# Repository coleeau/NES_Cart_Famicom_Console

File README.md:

# NES Cartridge Famicom Console
An adapter to use NES cartridges on a Famicom

## Why
Primarily so i can use NES Games that are either NES exclusive (ie Tetris) or cheaper overall (ie accounting for shipping and import fees)

## Why not buy one
a few reasons here
- Harder to find than the adapter for the other way around
- ones you can find are too expensive, and are bare pcb
- all existing ones have the cartridge vertically. wobble will be bad for connection and it looks stupid
- many existing ones lack expansion audio and other issues

## Goal for adapter
- Horizontal orientation for adapter (think famicom network adapter meets Blinking Light Win)
- support for either no expansion audio OR expansion audio on EXP6 or EXP9
- support for cartridges that requite CIRAM /CE and PPU /A14 to be sepearate

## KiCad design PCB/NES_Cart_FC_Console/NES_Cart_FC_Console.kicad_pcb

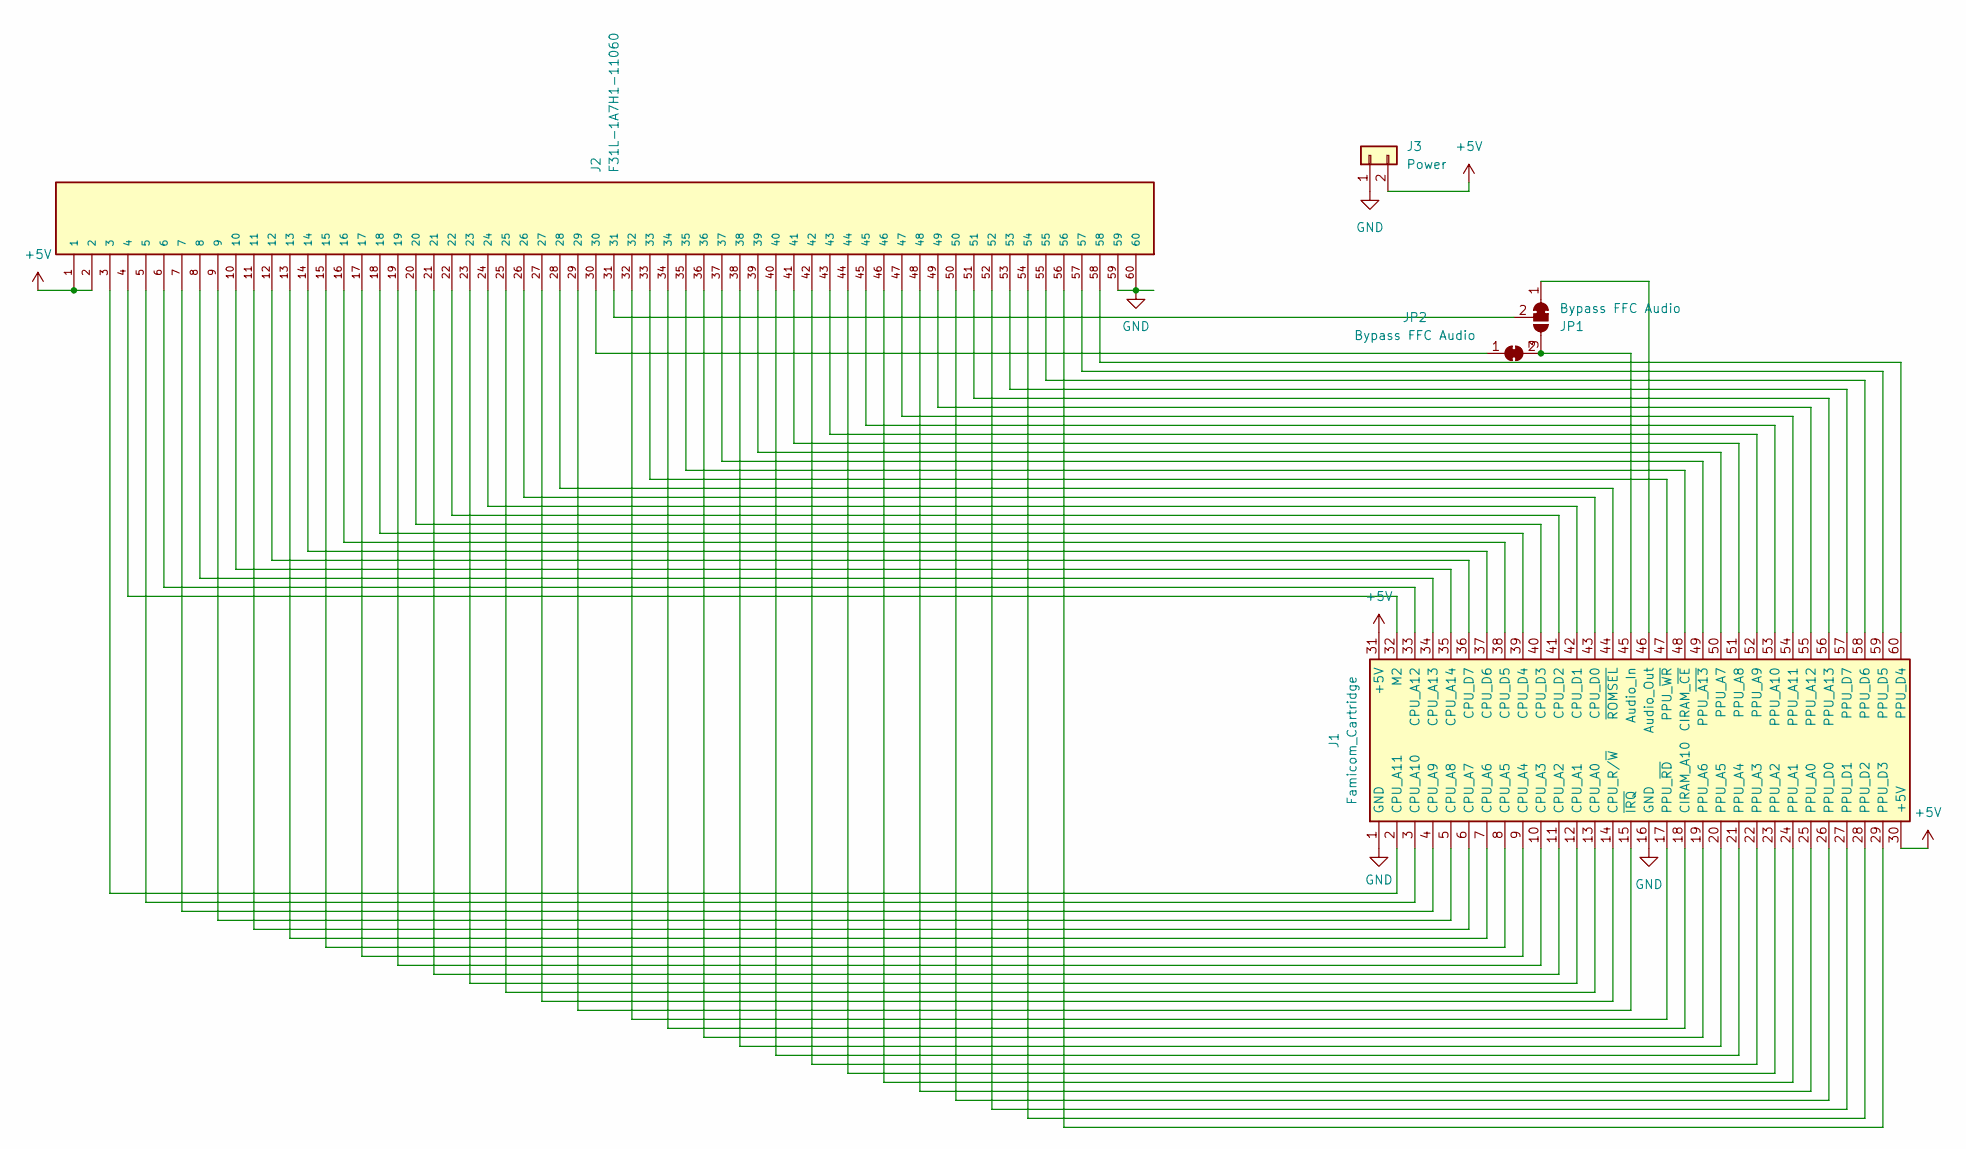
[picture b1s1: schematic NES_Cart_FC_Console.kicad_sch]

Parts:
J1: Famicom_Cartridge; Famicom_Card_Edge
J2: F31L-1A7H1-11060; AMPHENOL_F31L-1A7H1-11060; PARTREV F31L-1A7H1-11060
J3: Power; PinSocket_1x02_P2.54mm_Vertical
JP1: Bypass FFC Audio; SolderJumper-3_P1.3mm_Bridged2Bar12_RoundedPad1.0x1.5mm_Num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
JP2: Bypass FFC Audio; SolderJumper-2_P1.3mm_Bridged_RoundedPad1.0x1.5mm

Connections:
+5V: J1.30 (+5V), J1.31 (+5V), J2.1, J2.2, J3.2
GND: J1.1 (GND), J1.16 (GND), J2.59, J2.60, J3.1
unnamed: J1.45 (Audio_In), JP1.3 (B), JP2.2 (B)
unnamed: J1.46 (Audio_Out), JP1.1 (A)
unnamed: J1.18 (CIRAM_A10), J2.34
unnamed: J1.48 (CIRAM_~CE), J2.35
unnamed: J1.13 (CPU_A0), J2.25
unnamed: J1.12 (CPU_A1), J2.23
unnamed: J1.11 (CPU_A2), J2.21
unnamed: J1.10 (CPU_A3), J2.19
unnamed: J1.9 (CPU_A4), J2.17
unnamed: J1.8 (CPU_A5), J2.15
unnamed: J1.7 (CPU_A6), J2.13
unnamed: J1.6 (CPU_A7), J2.11
unnamed: J1.5 (CPU_A8), J2.9
unnamed: J1.4 (CPU_A9), J2.7
unnamed: J1.3 (CPU_A10), J2.5
unnamed: J1.2 (CPU_A11), J2.3
unnamed: J1.33 (CPU_A12), J2.6
unnamed: J1.34 (CPU_A13), J2.8
unnamed: J1.35 (CPU_A14), J2.10
unnamed: J1.43 (CPU_D0), J2.26
unnamed: J1.42 (CPU_D1), J2.24
unnamed: J1.41 (CPU_D2), J2.22
unnamed: J1.40 (CPU_D3), J2.20
unnamed: J1.39 (CPU_D4), J2.18
unnamed: J1.38 (CPU_D5), J2.16
unnamed: J1.37 (CPU_D6), J2.14
unnamed: J1.36 (CPU_D7), J2.12
unnamed: J1.14 (CPU_R/~W), J2.27
unnamed: J1.32 (M2), J2.4
unnamed: J1.25 (PPU_A0), J2.48
unnamed: J1.24 (PPU_A1), J2.46
unnamed: J1.23 (PPU_A2), J2.44
unnamed: J1.22 (PPU_A3), J2.42
unnamed: J1.21 (PPU_A4), J2.40
unnamed: J1.20 (PPU_A5), J2.38
unnamed: J1.19 (PPU_A6), J2.36
unnamed: J1.50 (PPU_A7), J2.39
unnamed: J1.51 (PPU_A8), J2.41
unnamed: J1.52 (PPU_A9), J2.43
unnamed: J1.53 (PPU_A10), J2.45
unnamed: J1.54 (PPU_A11), J2.47
unnamed: J1.55 (PPU_A12), J2.49
unnamed: J1.56 (PPU_A13), J2.51
unnamed: J1.26 (PPU_D0), J2.50
unnamed: J1.27 (PPU_D1), J2.52
unnamed: J1.28 (PPU_D2), J2.54
unnamed: J1.29 (PPU_D3), J2.56
unnamed: J1.60 (PPU_D4), J2.58
unnamed: J1.59 (PPU_D5), J2.57
unnamed: J1.58 (PPU_D6), J2.55
unnamed: J1.57 (PPU_D7), J2.53
unnamed: J1.49 (PPU_~A13), J2.37
unnamed: J1.17 (PPU_~RD), J2.32
unnamed: J1.47 (PPU_~WR), J2.33
unnamed: J1.15 (~IRQ), J2.29
unnamed: J1.44 (~ROMSEL), J2.28
unnamed: J2.31, JP1.2 (C)
unnamed: J2.30, JP2.1 (A)

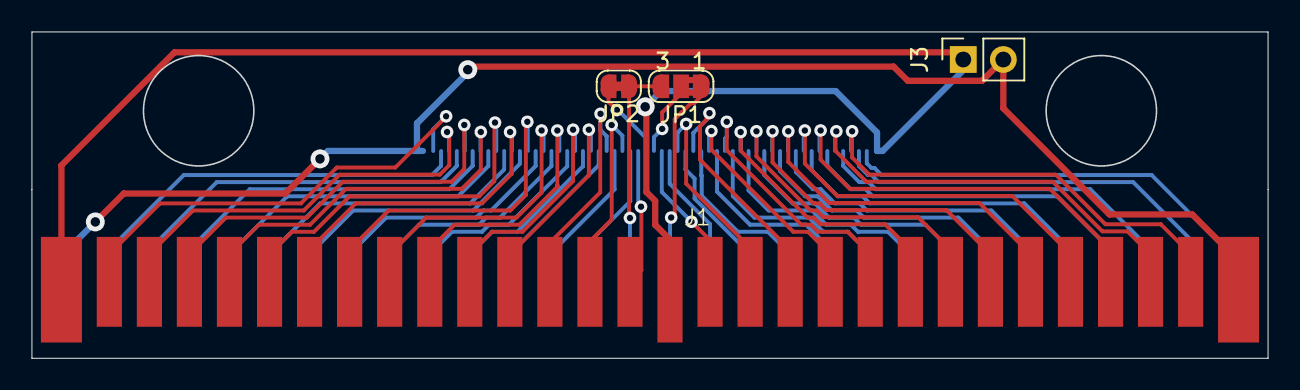
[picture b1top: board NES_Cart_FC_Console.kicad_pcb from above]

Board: 2 copper layers, 78.3 x 20.7 mm, 5 parts (1 on the bottom side), 60 nets.

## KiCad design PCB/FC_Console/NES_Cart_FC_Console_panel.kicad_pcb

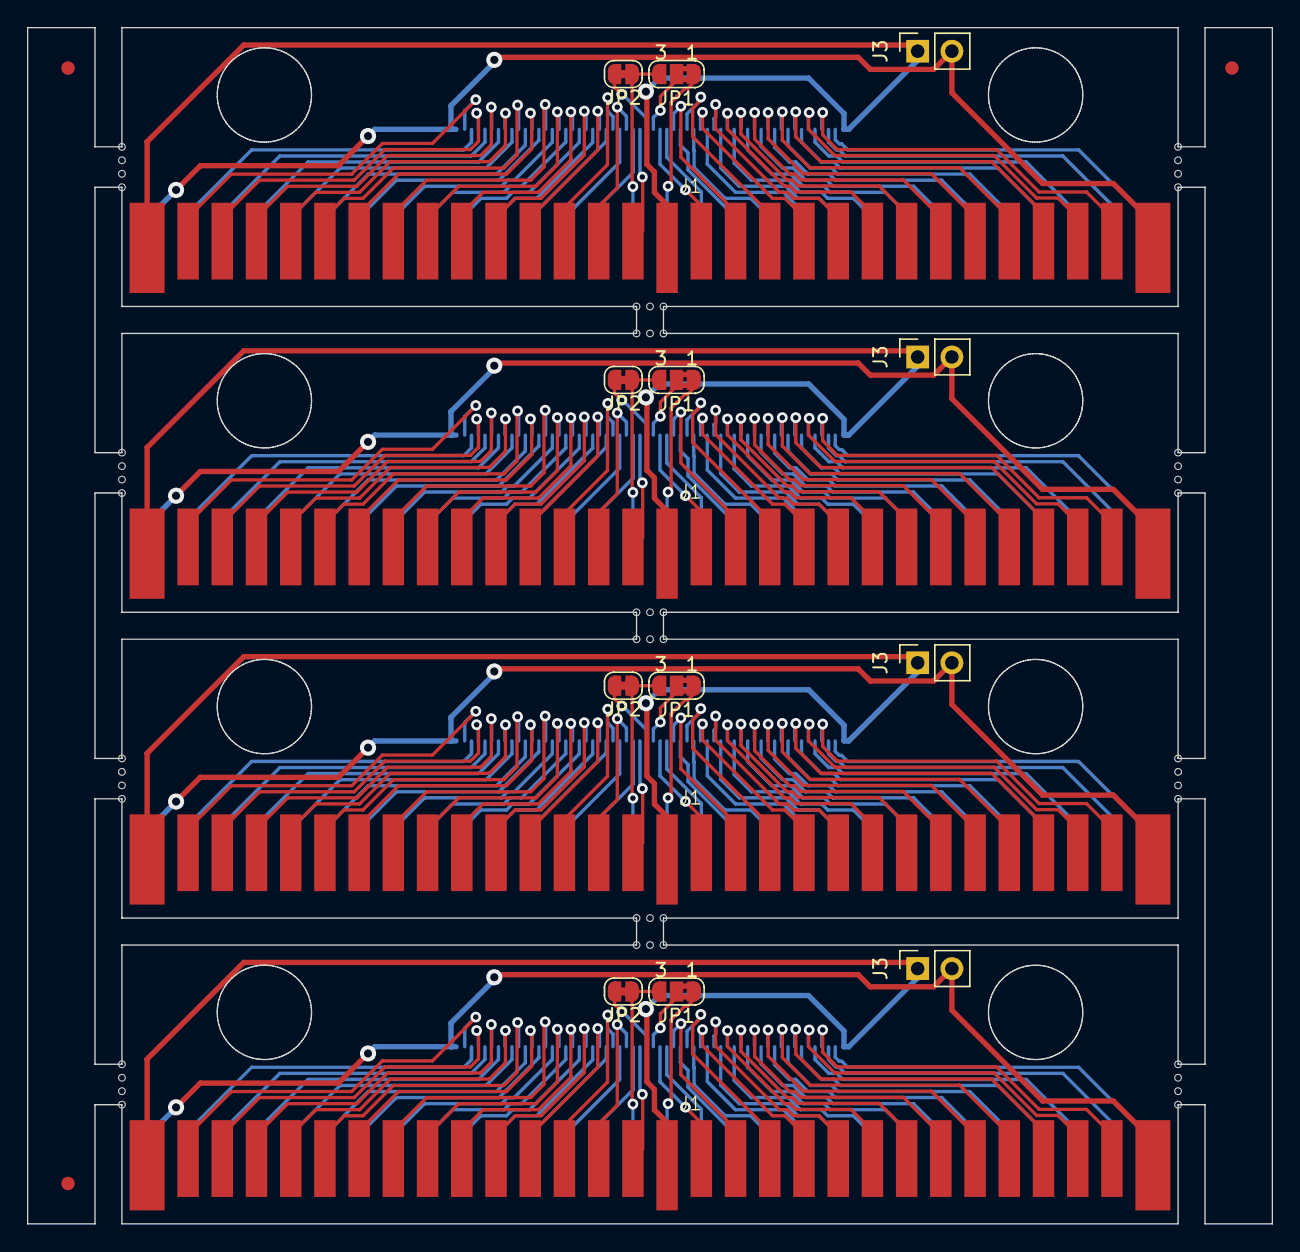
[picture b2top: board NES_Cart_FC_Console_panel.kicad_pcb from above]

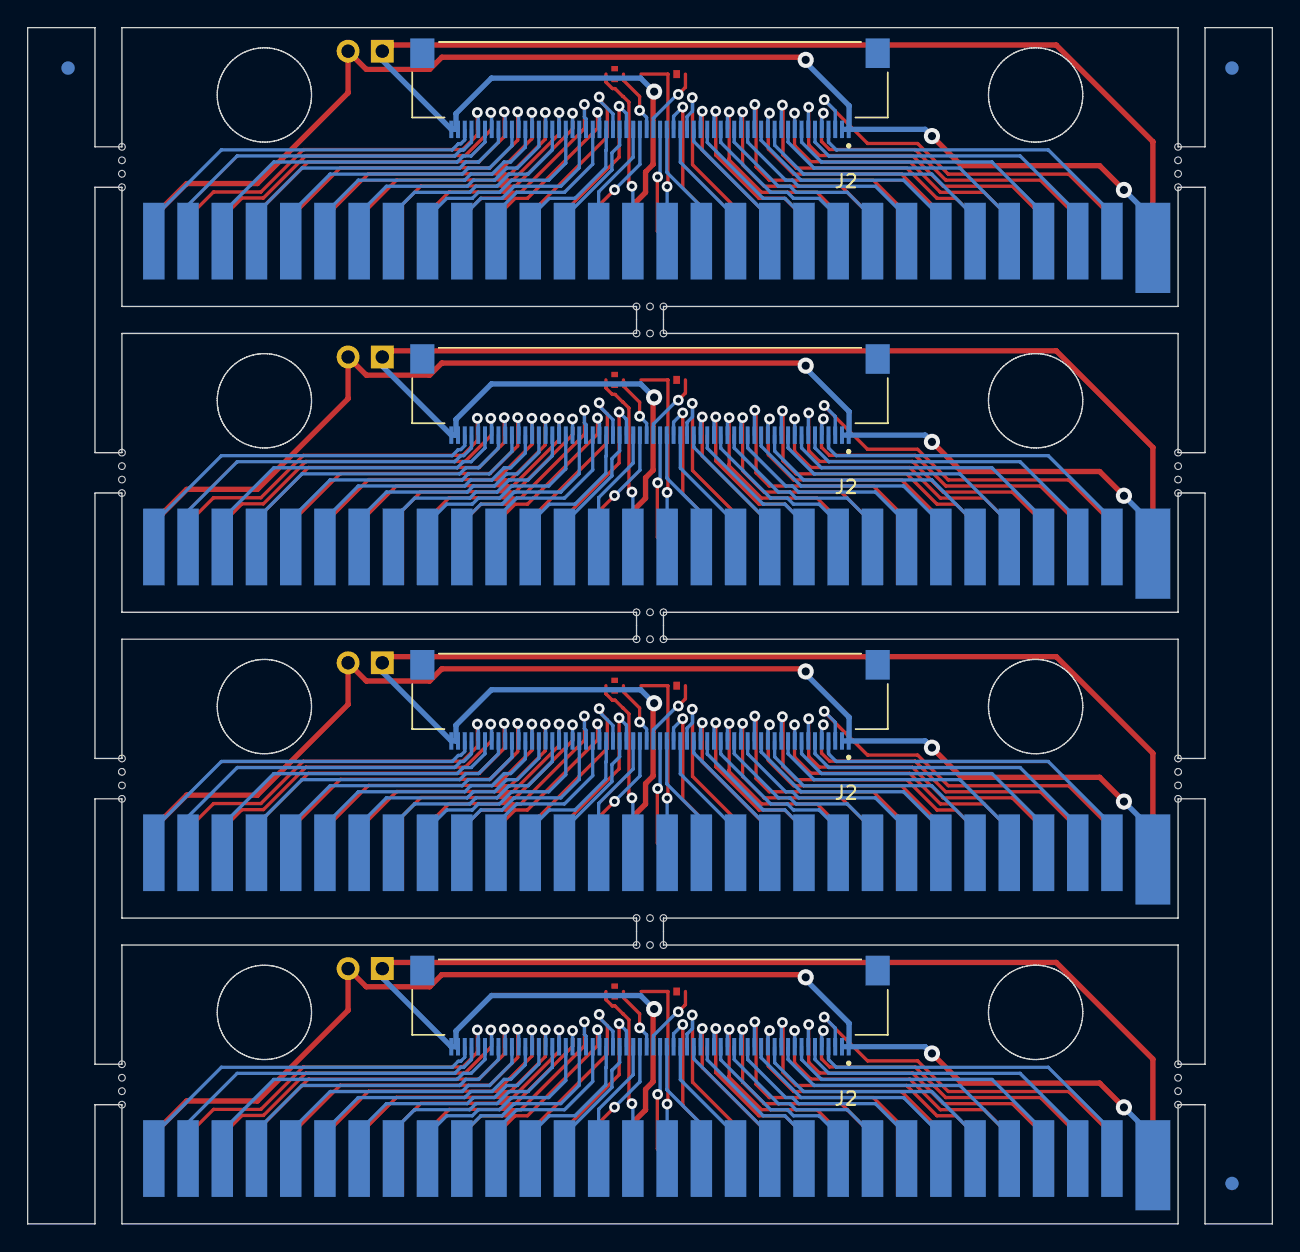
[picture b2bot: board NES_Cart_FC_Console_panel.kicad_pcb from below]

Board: 2 copper layers, 92.4 x 88.8 mm, 76 parts (7 on the bottom side), 240 nets.

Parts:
J1, J1#2, J1#3, J1#4: Famicom_Cartridge; Famicom_Card_Edge
J2, J2#2, J2#3, J2#4: F31L-1A7H1-11060; AMPHENOL_F31L-1A7H1-11060
J3, J3#2, J3#3, J3#4: Power; PinSocket_1x02_P2.54mm_Vertical
JP1, JP1#2, JP1#3, JP1#4: Bypass FFC Audio; SolderJumper-3_P1.3mm_Bridged2Bar12_RoundedPad1.0x1.5mm_Num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
JP2, JP2#2, JP2#3, JP2#4: Bypass FFC Audio; SolderJumper-2_P1.3mm_Bridged_RoundedPad1.0x1.5mm
KiKit_FID_B_1, KiKit_FID_B_2, KiKit_FID_B_3: Fiducial
KiKit_FID_T_1, KiKit_FID_T_2, KiKit_FID_T_3: Fiducial
KiKit_MB_1_1, KiKit_MB_1_2, KiKit_MB_1_3, KiKit_MB_1_4, KiKit_MB_2_1, KiKit_MB_2_2, KiKit_MB_2_3, KiKit_MB_2_4, KiKit_MB_3_1, KiKit_MB_3_2, KiKit_MB_3_3, KiKit_MB_4_1, KiKit_MB_4_2, KiKit_MB_4_3, KiKit_MB_4_4, KiKit_MB_5_1, KiKit_MB_5_2, KiKit_MB_5_3, KiKit_MB_5_4, KiKit_MB_6_1, KiKit_MB_6_2, KiKit_MB_6_3, KiKit_MB_7_1, KiKit_MB_7_2, KiKit_MB_7_3, KiKit_MB_8_1, KiKit_MB_8_2, KiKit_MB_8_3, KiKit_MB_8_4, KiKit_MB_9_1, KiKit_MB_9_2, KiKit_MB_9_3, KiKit_MB_9_4, KiKit_MB_10_1, KiKit_MB_10_2, KiKit_MB_10_3, KiKit_MB_11_1, KiKit_MB_11_2, KiKit_MB_11_3, KiKit_MB_12_1, KiKit_MB_12_2, KiKit_MB_12_3, KiKit_MB_12_4, KiKit_MB_13_1, KiKit_MB_13_2, KiKit_MB_13_3, KiKit_MB_13_4, KiKit_MB_14_1, KiKit_MB_14_2, KiKit_MB_14_3: NPTH

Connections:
Board_0-+5V: J1.30 (+5V), J1.31 (+5V), J2.1, J2.2, J3#4.2
Board_0-GND: J1.1 (GND), J1.16 (GND), J2.59, J2.60, J3#4.1
Board_0-Net-(J1-Audio_In): J1.45 (Audio_In), JP1#4.3 (B), JP2.2 (B)
Board_0-Net-(J1-Audio_Out): J1.46 (Audio_Out), JP1#4.1 (A)
Board_0-Net-(J1-CIRAM_A10): J1.18 (CIRAM_A10), J2.34
Board_0-Net-(J1-CIRAM_~CE): J1.48 (CIRAM_~CE), J2.35
Board_0-Net-(J1-CPU_A0): J1.13 (CPU_A0), J2.25
Board_0-Net-(J1-CPU_A1): J1.12 (CPU_A1), J2.23
Board_0-Net-(J1-CPU_A2): J1.11 (CPU_A2), J2.21
Board_0-Net-(J1-CPU_A3): J1.10 (CPU_A3), J2.19
Board_0-Net-(J1-CPU_A4): J1.9 (CPU_A4), J2.17
Board_0-Net-(J1-CPU_A5): J1.8 (CPU_A5), J2.15
Board_0-Net-(J1-CPU_A6): J1.7 (CPU_A6), J2.13
Board_0-Net-(J1-CPU_A7): J1.6 (CPU_A7), J2.11
Board_0-Net-(J1-CPU_A8): J1.5 (CPU_A8), J2.9
Board_0-Net-(J1-CPU_A9): J1.4 (CPU_A9), J2.7
Board_0-Net-(J1-CPU_A10): J1.3 (CPU_A10), J2.5
Board_0-Net-(J1-CPU_A11): J1.2 (CPU_A11), J2.3
Board_0-Net-(J1-CPU_A12): J1.33 (CPU_A12), J2.6
Board_0-Net-(J1-CPU_A13): J1.34 (CPU_A13), J2.8
Board_0-Net-(J1-CPU_A14): J1.35 (CPU_A14), J2.10
Board_0-Net-(J1-CPU_D0): J1.43 (CPU_D0), J2.26
Board_0-Net-(J1-CPU_D1): J1.42 (CPU_D1), J2.24
Board_0-Net-(J1-CPU_D2): J1.41 (CPU_D2), J2.22
Board_0-Net-(J1-CPU_D3): J1.40 (CPU_D3), J2.20
Board_0-Net-(J1-CPU_D4): J1.39 (CPU_D4), J2.18
Board_0-Net-(J1-CPU_D5): J1.38 (CPU_D5), J2.16
Board_0-Net-(J1-CPU_D6): J1.37 (CPU_D6), J2.14
Board_0-Net-(J1-CPU_D7): J1.36 (CPU_D7), J2.12
Board_0-Net-(J1-CPU_R/~W): J1.14 (CPU_R/~W), J2.27
Board_0-Net-(J1-M2): J1.32 (M2), J2.4
Board_0-Net-(J1-PPU_A0): J1.25 (PPU_A0), J2.48
Board_0-Net-(J1-PPU_A1): J1.24 (PPU_A1), J2.46
Board_0-Net-(J1-PPU_A2): J1.23 (PPU_A2), J2.44
Board_0-Net-(J1-PPU_A3): J1.22 (PPU_A3), J2.42
Board_0-Net-(J1-PPU_A4): J1.21 (PPU_A4), J2.40
Board_0-Net-(J1-PPU_A5): J1.20 (PPU_A5), J2.38
Board_0-Net-(J1-PPU_A6): J1.19 (PPU_A6), J2.36
Board_0-Net-(J1-PPU_A7): J1.50 (PPU_A7), J2.39
Board_0-Net-(J1-PPU_A8): J1.51 (PPU_A8), J2.41
Board_0-Net-(J1-PPU_A9): J1.52 (PPU_A9), J2.43
Board_0-Net-(J1-PPU_A10): J1.53 (PPU_A10), J2.45
Board_0-Net-(J1-PPU_A11): J1.54 (PPU_A11), J2.47
Board_0-Net-(J1-PPU_A12): J1.55 (PPU_A12), J2.49
Board_0-Net-(J1-PPU_A13): J1.56 (PPU_A13), J2.51
Board_0-Net-(J1-PPU_D0): J1.26 (PPU_D0), J2.50
Board_0-Net-(J1-PPU_D1): J1.27 (PPU_D1), J2.52
Board_0-Net-(J1-PPU_D2): J1.28 (PPU_D2), J2.54
Board_0-Net-(J1-PPU_D3): J1.29 (PPU_D3), J2.56
Board_0-Net-(J1-PPU_D4): J1.60 (PPU_D4), J2.58
Board_0-Net-(J1-PPU_D5): J1.59 (PPU_D5), J2.57
Board_0-Net-(J1-PPU_D6): J1.58 (PPU_D6), J2.55
Board_0-Net-(J1-PPU_D7): J1.57 (PPU_D7), J2.53
Board_0-Net-(J1-PPU_~A13): J1.49 (PPU_~A13), J2.37
Board_0-Net-(J1-PPU_~RD): J1.17 (PPU_~RD), J2.32
Board_0-Net-(J1-PPU_~WR): J1.47 (PPU_~WR), J2.33
Board_0-Net-(J1-~IRQ): J1.15 (~IRQ), J2.29
Board_0-Net-(J1-~ROMSEL): J1.44 (~ROMSEL), J2.28
Board_0-Net-(JP1-C): J2.31, JP1#4.2 (C)
Board_0-Net-(JP2-A): J2.30, JP2.1 (A)
Board_1-+5V: J1#3.30 (+5V), J1#3.31 (+5V), J2#4.1, J2#4.2, J3#3.2
Board_1-GND: J1#3.1 (GND), J1#3.16 (GND), J2#4.59, J2#4.60, J3#3.1
Board_1-Net-(J1-Audio_In): J1#3.45 (Audio_In), JP1#3.3 (B), JP2#3.2 (B)
Board_1-Net-(J1-Audio_Out): J1#3.46 (Audio_Out), JP1#3.1 (A)
Board_1-Net-(J1-CIRAM_A10): J1#3.18 (CIRAM_A10), J2#4.34
Board_1-Net-(J1-CIRAM_~CE): J1#3.48 (CIRAM_~CE), J2#4.35
Board_1-Net-(J1-CPU_A0): J1#3.13 (CPU_A0), J2#4.25
Board_1-Net-(J1-CPU_A1): J1#3.12 (CPU_A1), J2#4.23
Board_1-Net-(J1-CPU_A2): J1#3.11 (CPU_A2), J2#4.21
Board_1-Net-(J1-CPU_A3): J1#3.10 (CPU_A3), J2#4.19
Board_1-Net-(J1-CPU_A4): J1#3.9 (CPU_A4), J2#4.17
Board_1-Net-(J1-CPU_A5): J1#3.8 (CPU_A5), J2#4.15
Board_1-Net-(J1-CPU_A6): J1#3.7 (CPU_A6), J2#4.13
Board_1-Net-(J1-CPU_A7): J1#3.6 (CPU_A7), J2#4.11
Board_1-Net-(J1-CPU_A8): J1#3.5 (CPU_A8), J2#4.9
Board_1-Net-(J1-CPU_A9): J1#3.4 (CPU_A9), J2#4.7
Board_1-Net-(J1-CPU_A10): J1#3.3 (CPU_A10), J2#4.5
Board_1-Net-(J1-CPU_A11): J1#3.2 (CPU_A11), J2#4.3
Board_1-Net-(J1-CPU_A12): J1#3.33 (CPU_A12), J2#4.6
Board_1-Net-(J1-CPU_A13): J1#3.34 (CPU_A13), J2#4.8
Board_1-Net-(J1-CPU_A14): J1#3.35 (CPU_A14), J2#4.10
Board_1-Net-(J1-CPU_D0): J1#3.43 (CPU_D0), J2#4.26
Board_1-Net-(J1-CPU_D1): J1#3.42 (CPU_D1), J2#4.24
Board_1-Net-(J1-CPU_D2): J1#3.41 (CPU_D2), J2#4.22
Board_1-Net-(J1-CPU_D3): J1#3.40 (CPU_D3), J2#4.20
Board_1-Net-(J1-CPU_D4): J1#3.39 (CPU_D4), J2#4.18
Board_1-Net-(J1-CPU_D5): J1#3.38 (CPU_D5), J2#4.16
Board_1-Net-(J1-CPU_D6): J1#3.37 (CPU_D6), J2#4.14
Board_1-Net-(J1-CPU_D7): J1#3.36 (CPU_D7), J2#4.12
Board_1-Net-(J1-CPU_R/~W): J1#3.14 (CPU_R/~W), J2#4.27
Board_1-Net-(J1-M2): J1#3.32 (M2), J2#4.4
Board_1-Net-(J1-PPU_A0): J1#3.25 (PPU_A0), J2#4.48
Board_1-Net-(J1-PPU_A1): J1#3.24 (PPU_A1), J2#4.46
Board_1-Net-(J1-PPU_A2): J1#3.23 (PPU_A2), J2#4.44
Board_1-Net-(J1-PPU_A3): J1#3.22 (PPU_A3), J2#4.42
Board_1-Net-(J1-PPU_A4): J1#3.21 (PPU_A4), J2#4.40
Board_1-Net-(J1-PPU_A5): J1#3.20 (PPU_A5), J2#4.38
Board_1-Net-(J1-PPU_A6): J1#3.19 (PPU_A6), J2#4.36
Board_1-Net-(J1-PPU_A7): J1#3.50 (PPU_A7), J2#4.39
Board_1-Net-(J1-PPU_A8): J1#3.51 (PPU_A8), J2#4.41
Board_1-Net-(J1-PPU_A9): J1#3.52 (PPU_A9), J2#4.43
Board_1-Net-(J1-PPU_A10): J1#3.53 (PPU_A10), J2#4.45
Board_1-Net-(J1-PPU_A11): J1#3.54 (PPU_A11), J2#4.47
Board_1-Net-(J1-PPU_A12): J1#3.55 (PPU_A12), J2#4.49
Board_1-Net-(J1-PPU_A13): J1#3.56 (PPU_A13), J2#4.51
Board_1-Net-(J1-PPU_D0): J1#3.26 (PPU_D0), J2#4.50
Board_1-Net-(J1-PPU_D1): J1#3.27 (PPU_D1), J2#4.52
Board_1-Net-(J1-PPU_D2): J1#3.28 (PPU_D2), J2#4.54
Board_1-Net-(J1-PPU_D3): J1#3.29 (PPU_D3), J2#4.56
Board_1-Net-(J1-PPU_D4): J1#3.60 (PPU_D4), J2#4.58
Board_1-Net-(J1-PPU_D5): J1#3.59 (PPU_D5), J2#4.57
Board_1-Net-(J1-PPU_D6): J1#3.58 (PPU_D6), J2#4.55
Board_1-Net-(J1-PPU_D7): J1#3.57 (PPU_D7), J2#4.53
Board_1-Net-(J1-PPU_~A13): J1#3.49 (PPU_~A13), J2#4.37
Board_1-Net-(J1-PPU_~RD): J1#3.17 (PPU_~RD), J2#4.32
Board_1-Net-(J1-PPU_~WR): J1#3.47 (PPU_~WR), J2#4.33
Board_1-Net-(J1-~IRQ): J1#3.15 (~IRQ), J2#4.29
Board_1-Net-(J1-~ROMSEL): J1#3.44 (~ROMSEL), J2#4.28
Board_1-Net-(JP1-C): J2#4.31, JP1#3.2 (C)
Board_1-Net-(JP2-A): J2#4.30, JP2#3.1 (A)
Board_2-+5V: J1#4.30 (+5V), J1#4.31 (+5V), J2#3.1, J2#3.2, J3#2.2
Board_2-GND: J1#4.1 (GND), J1#4.16 (GND), J2#3.59, J2#3.60, J3#2.1
Board_2-Net-(J1-Audio_In): J1#4.45 (Audio_In), JP1.3 (B), JP2#4.2 (B)
Board_2-Net-(J1-Audio_Out): J1#4.46 (Audio_Out), JP1.1 (A)
Board_2-Net-(J1-CIRAM_A10): J1#4.18 (CIRAM_A10), J2#3.34
Board_2-Net-(J1-CIRAM_~CE): J1#4.48 (CIRAM_~CE), J2#3.35
Board_2-Net-(J1-CPU_A0): J1#4.13 (CPU_A0), J2#3.25
Board_2-Net-(J1-CPU_A1): J1#4.12 (CPU_A1), J2#3.23
Board_2-Net-(J1-CPU_A2): J1#4.11 (CPU_A2), J2#3.21
Board_2-Net-(J1-CPU_A3): J1#4.10 (CPU_A3), J2#3.19
Board_2-Net-(J1-CPU_A4): J1#4.9 (CPU_A4), J2#3.17
Board_2-Net-(J1-CPU_A5): J1#4.8 (CPU_A5), J2#3.15
Board_2-Net-(J1-CPU_A6): J1#4.7 (CPU_A6), J2#3.13
Board_2-Net-(J1-CPU_A7): J1#4.6 (CPU_A7), J2#3.11
Board_2-Net-(J1-CPU_A8): J1#4.5 (CPU_A8), J2#3.9
Board_2-Net-(J1-CPU_A9): J1#4.4 (CPU_A9), J2#3.7
Board_2-Net-(J1-CPU_A10): J1#4.3 (CPU_A10), J2#3.5
Board_2-Net-(J1-CPU_A11): J1#4.2 (CPU_A11), J2#3.3
Board_2-Net-(J1-CPU_A12): J1#4.33 (CPU_A12), J2#3.6
Board_2-Net-(J1-CPU_A13): J1#4.34 (CPU_A13), J2#3.8
Board_2-Net-(J1-CPU_A14): J1#4.35 (CPU_A14), J2#3.10
Board_2-Net-(J1-CPU_D0): J1#4.43 (CPU_D0), J2#3.26
Board_2-Net-(J1-CPU_D1): J1#4.42 (CPU_D1), J2#3.24
Board_2-Net-(J1-CPU_D2): J1#4.41 (CPU_D2), J2#3.22
Board_2-Net-(J1-CPU_D3): J1#4.40 (CPU_D3), J2#3.20
Board_2-Net-(J1-CPU_D4): J1#4.39 (CPU_D4), J2#3.18
Board_2-Net-(J1-CPU_D5): J1#4.38 (CPU_D5), J2#3.16
Board_2-Net-(J1-CPU_D6): J1#4.37 (CPU_D6), J2#3.14
Board_2-Net-(J1-CPU_D7): J1#4.36 (CPU_D7), J2#3.12
Board_2-Net-(J1-CPU_R/~W): J1#4.14 (CPU_R/~W), J2#3.27
Board_2-Net-(J1-M2): J1#4.32 (M2), J2#3.4
Board_2-Net-(J1-PPU_A0): J1#4.25 (PPU_A0), J2#3.48
Board_2-Net-(J1-PPU_A1): J1#4.24 (PPU_A1), J2#3.46
Board_2-Net-(J1-PPU_A2): J1#4.23 (PPU_A2), J2#3.44
Board_2-Net-(J1-PPU_A3): J1#4.22 (PPU_A3), J2#3.42
Board_2-Net-(J1-PPU_A4): J1#4.21 (PPU_A4), J2#3.40
Board_2-Net-(J1-PPU_A5): J1#4.20 (PPU_A5), J2#3.38
Board_2-Net-(J1-PPU_A6): J1#4.19 (PPU_A6), J2#3.36
Board_2-Net-(J1-PPU_A7): J1#4.50 (PPU_A7), J2#3.39
Board_2-Net-(J1-PPU_A8): J1#4.51 (PPU_A8), J2#3.41
Board_2-Net-(J1-PPU_A9): J1#4.52 (PPU_A9), J2#3.43
Board_2-Net-(J1-PPU_A10): J1#4.53 (PPU_A10), J2#3.45
Board_2-Net-(J1-PPU_A11): J1#4.54 (PPU_A11), J2#3.47
Board_2-Net-(J1-PPU_A12): J1#4.55 (PPU_A12), J2#3.49
Board_2-Net-(J1-PPU_A13): J1#4.56 (PPU_A13), J2#3.51
Board_2-Net-(J1-PPU_D0): J1#4.26 (PPU_D0), J2#3.50
Board_2-Net-(J1-PPU_D1): J1#4.27 (PPU_D1), J2#3.52
Board_2-Net-(J1-PPU_D2): J1#4.28 (PPU_D2), J2#3.54
Board_2-Net-(J1-PPU_D3): J1#4.29 (PPU_D3), J2#3.56
Board_2-Net-(J1-PPU_D4): J1#4.60 (PPU_D4), J2#3.58
Board_2-Net-(J1-PPU_D5): J1#4.59 (PPU_D5), J2#3.57
Board_2-Net-(J1-PPU_D6): J1#4.58 (PPU_D6), J2#3.55
Board_2-Net-(J1-PPU_D7): J1#4.57 (PPU_D7), J2#3.53
Board_2-Net-(J1-PPU_~A13): J1#4.49 (PPU_~A13), J2#3.37
Board_2-Net-(J1-PPU_~RD): J1#4.17 (PPU_~RD), J2#3.32
Board_2-Net-(J1-PPU_~WR): J1#4.47 (PPU_~WR), J2#3.33
Board_2-Net-(J1-~IRQ): J1#4.15 (~IRQ), J2#3.29
Board_2-Net-(J1-~ROMSEL): J1#4.44 (~ROMSEL), J2#3.28
Board_2-Net-(JP1-C): J2#3.31, JP1.2 (C)
Board_2-Net-(JP2-A): J2#3.30, JP2#4.1 (A)
Board_3-+5V: J1#2.30 (+5V), J1#2.31 (+5V), J2#2.1, J2#2.2, J3.2
Board_3-GND: J1#2.1 (GND), J1#2.16 (GND), J2#2.59, J2#2.60, J3.1
Board_3-Net-(J1-Audio_In): J1#2.45 (Audio_In), JP1#2.3 (B), JP2#2.2 (B)
Board_3-Net-(J1-Audio_Out): J1#2.46 (Audio_Out), JP1#2.1 (A)
Board_3-Net-(J1-CIRAM_A10): J1#2.18 (CIRAM_A10), J2#2.34
Board_3-Net-(J1-CIRAM_~CE): J1#2.48 (CIRAM_~CE), J2#2.35
Board_3-Net-(J1-CPU_A0): J1#2.13 (CPU_A0), J2#2.25
Board_3-Net-(J1-CPU_A1): J1#2.12 (CPU_A1), J2#2.23
Board_3-Net-(J1-CPU_A2): J1#2.11 (CPU_A2), J2#2.21
Board_3-Net-(J1-CPU_A3): J1#2.10 (CPU_A3), J2#2.19
Board_3-Net-(J1-CPU_A4): J1#2.9 (CPU_A4), J2#2.17
Board_3-Net-(J1-CPU_A5): J1#2.8 (CPU_A5), J2#2.15
Board_3-Net-(J1-CPU_A6): J1#2.7 (CPU_A6), J2#2.13
Board_3-Net-(J1-CPU_A7): J1#2.6 (CPU_A7), J2#2.11
Board_3-Net-(J1-CPU_A8): J1#2.5 (CPU_A8), J2#2.9
Board_3-Net-(J1-CPU_A9): J1#2.4 (CPU_A9), J2#2.7
Board_3-Net-(J1-CPU_A10): J1#2.3 (CPU_A10), J2#2.5
Board_3-Net-(J1-CPU_A11): J1#2.2 (CPU_A11), J2#2.3
Board_3-Net-(J1-CPU_A12): J1#2.33 (CPU_A12), J2#2.6
Board_3-Net-(J1-CPU_A13): J1#2.34 (CPU_A13), J2#2.8
Board_3-Net-(J1-CPU_A14): J1#2.35 (CPU_A14), J2#2.10
Board_3-Net-(J1-CPU_D0): J1#2.43 (CPU_D0), J2#2.26
Board_3-Net-(J1-CPU_D1): J1#2.42 (CPU_D1), J2#2.24
Board_3-Net-(J1-CPU_D2): J1#2.41 (CPU_D2), J2#2.22
Board_3-Net-(J1-CPU_D3): J1#2.40 (CPU_D3), J2#2.20
Board_3-Net-(J1-CPU_D4): J1#2.39 (CPU_D4), J2#2.18
Board_3-Net-(J1-CPU_D5): J1#2.38 (CPU_D5), J2#2.16
Board_3-Net-(J1-CPU_D6): J1#2.37 (CPU_D6), J2#2.14
Board_3-Net-(J1-CPU_D7): J1#2.36 (CPU_D7), J2#2.12
Board_3-Net-(J1-CPU_R/~W): J1#2.14 (CPU_R/~W), J2#2.27
Board_3-Net-(J1-M2): J1#2.32 (M2), J2#2.4
Board_3-Net-(J1-PPU_A0): J1#2.25 (PPU_A0), J2#2.48
Board_3-Net-(J1-PPU_A1): J1#2.24 (PPU_A1), J2#2.46
Board_3-Net-(J1-PPU_A2): J1#2.23 (PPU_A2), J2#2.44
Board_3-Net-(J1-PPU_A3): J1#2.22 (PPU_A3), J2#2.42
Board_3-Net-(J1-PPU_A4): J1#2.21 (PPU_A4), J2#2.40
Board_3-Net-(J1-PPU_A5): J1#2.20 (PPU_A5), J2#2.38
Board_3-Net-(J1-PPU_A6): J1#2.19 (PPU_A6), J2#2.36
Board_3-Net-(J1-PPU_A7): J1#2.50 (PPU_A7), J2#2.39
Board_3-Net-(J1-PPU_A8): J1#2.51 (PPU_A8), J2#2.41
Board_3-Net-(J1-PPU_A9): J1#2.52 (PPU_A9), J2#2.43
Board_3-Net-(J1-PPU_A10): J1#2.53 (PPU_A10), J2#2.45
Board_3-Net-(J1-PPU_A11): J1#2.54 (PPU_A11), J2#2.47
Board_3-Net-(J1-PPU_A12): J1#2.55 (PPU_A12), J2#2.49
Board_3-Net-(J1-PPU_A13): J1#2.56 (PPU_A13), J2#2.51
Board_3-Net-(J1-PPU_D0): J1#2.26 (PPU_D0), J2#2.50
Board_3-Net-(J1-PPU_D1): J1#2.27 (PPU_D1), J2#2.52
Board_3-Net-(J1-PPU_D2): J1#2.28 (PPU_D2), J2#2.54
Board_3-Net-(J1-PPU_D3): J1#2.29 (PPU_D3), J2#2.56
Board_3-Net-(J1-PPU_D4): J1#2.60 (PPU_D4), J2#2.58
Board_3-Net-(J1-PPU_D5): J1#2.59 (PPU_D5), J2#2.57
Board_3-Net-(J1-PPU_D6): J1#2.58 (PPU_D6), J2#2.55
Board_3-Net-(J1-PPU_D7): J1#2.57 (PPU_D7), J2#2.53
Board_3-Net-(J1-PPU_~A13): J1#2.49 (PPU_~A13), J2#2.37
Board_3-Net-(J1-PPU_~RD): J1#2.17 (PPU_~RD), J2#2.32
Board_3-Net-(J1-PPU_~WR): J1#2.47 (PPU_~WR), J2#2.33
Board_3-Net-(J1-~IRQ): J1#2.15 (~IRQ), J2#2.29
Board_3-Net-(J1-~ROMSEL): J1#2.44 (~ROMSEL), J2#2.28
Board_3-Net-(JP1-C): J2#2.31, JP1#2.2 (C)
Board_3-Net-(JP2-A): J2#2.30, JP2#2.1 (A)

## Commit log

2024-03-05 Initial
2024-04-11 additional work done
2024-07-13 reorganized file tree, started work on nes portion
